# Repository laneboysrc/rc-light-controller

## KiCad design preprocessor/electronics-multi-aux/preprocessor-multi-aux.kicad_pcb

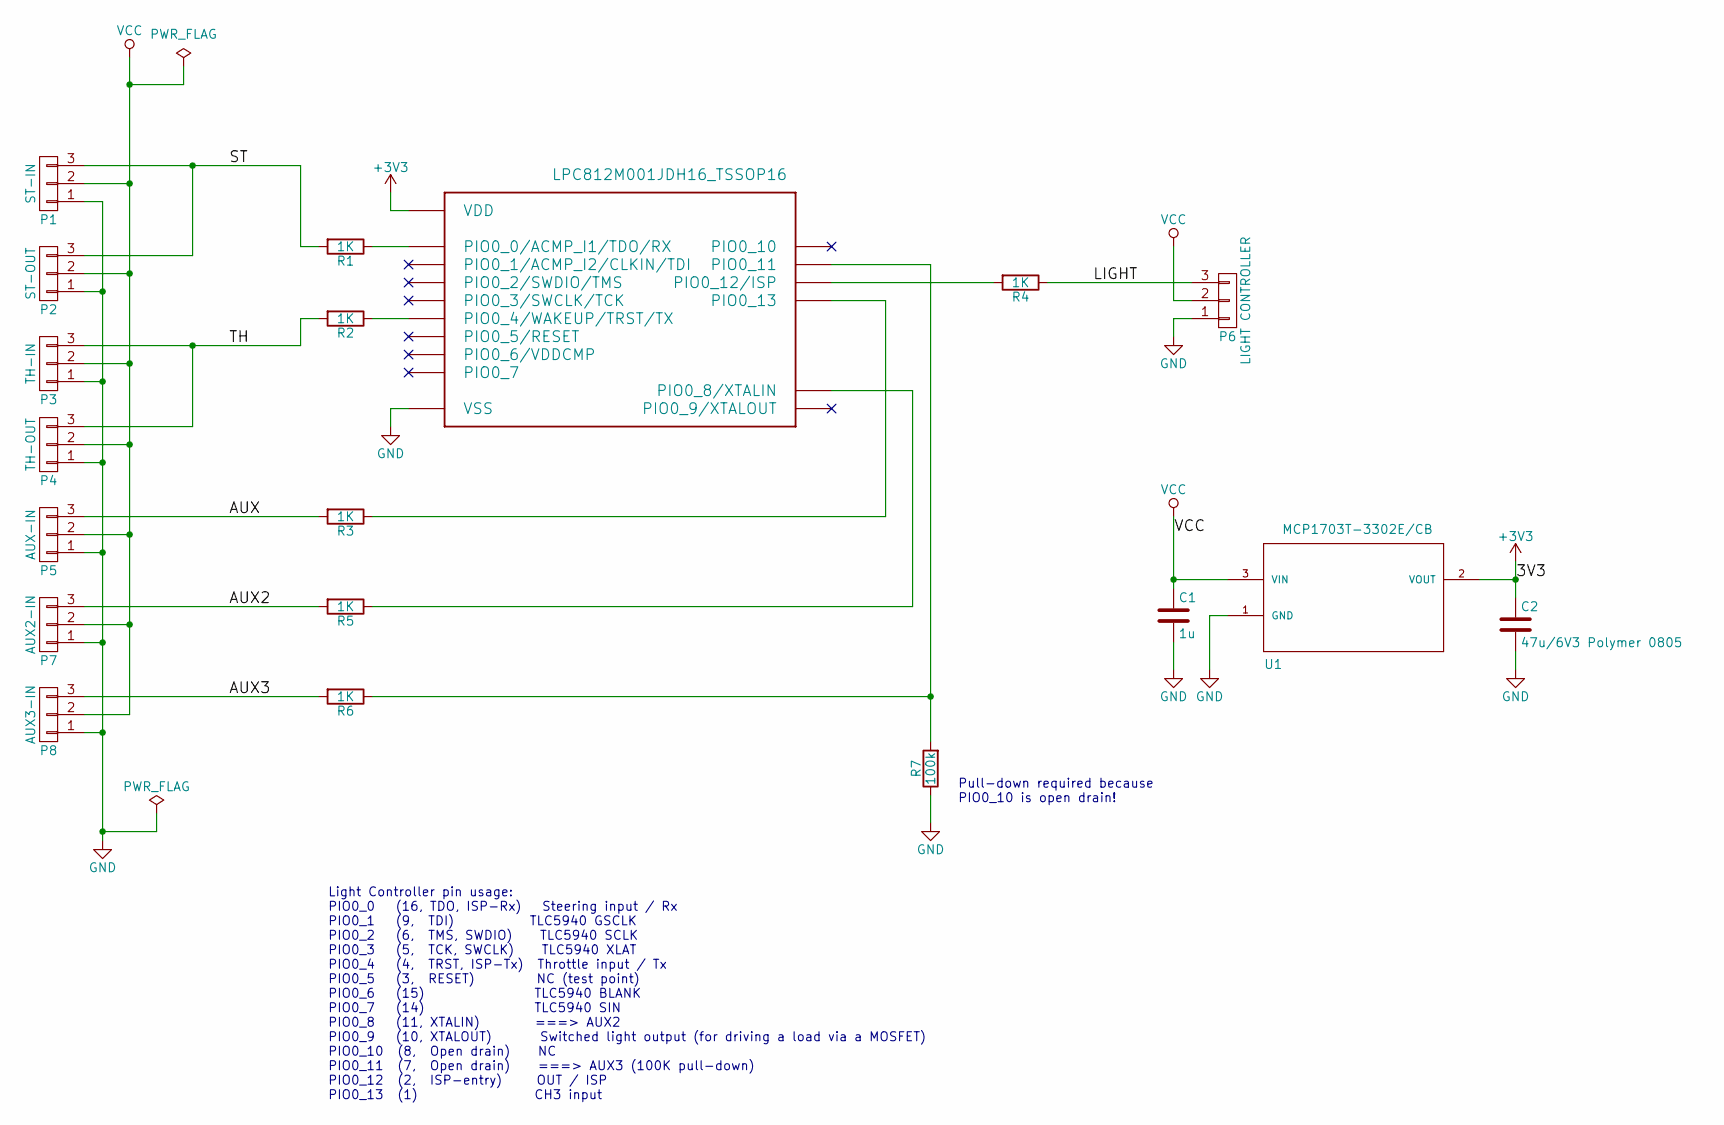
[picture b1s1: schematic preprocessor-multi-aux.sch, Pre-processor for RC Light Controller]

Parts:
C1: 1u; C_0805_2012Metric_Pad1.15x1.40mm_HandSolder
C2: 47u/6V3 Polymer 0805; C_0805_2012Metric_Pad1.15x1.40mm_HandSolder
P1: ST-IN; PinHeader_1x03_P2.54mm_Vertical
P2: ST-OUT; PinHeader_1x03_P2.54mm_Vertical
P3: TH-IN; PinHeader_1x03_P2.54mm_Vertical
P4: TH-OUT; PinHeader_1x03_P2.54mm_Vertical
P5: AUX-IN; PinHeader_1x03_P2.54mm_Vertical
P6: LIGHT CONTROLLER; PinHeader_1x03_P2.54mm_Vertical
P7: AUX2-IN; PinHeader_1x03_P2.54mm_Vertical
P8: AUX3-IN; PinHeader_1x03_P2.54mm_Vertical
R1, R2, R3, R4, R5, R6: 1K; R_0603_1608Metric_Pad1.05x0.95mm_HandSolder
R7: 100k; R_0603_1608Metric_Pad1.05x0.95mm_HandSolder
U1: MCP1703T-3302E/CB; SOT-23W_Handsoldering
U2: LPC812M001JDH16_TSSOP16; TSSOP-16_4.4x5mm_P0.65mm

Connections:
+3V3: C2.1, U1.2 (VOUT), U2.12 (VDD)
/AUX: P5.3, R3.2
/AUX2: P7.3, R5.2
/AUX3: P8.3, R6.2
/LIGHT: P6.3, R4.1
/ST: P1.3, P2.3, R1.2
/TH: P3.3, P4.3, R2.2
GND: C1.2, C2.2, P1.1, P2.1, P3.1, P4.1, P5.1, P6.1, P7.1, P8.1, R7.1, U1.1 (GND), U2.13 (VSS)
unnamed: R1.1, U2.16 (PIO0_0/ACMP_I1/TDO/RX)
unnamed: R2.1, U2.4 (PIO0_4/WAKEUP/TRST/TX)
unnamed: R3.1, U2.1 (PIO0_13)
unnamed: R4.2, U2.2 (PIO0_12/ISP)
unnamed: R5.1, U2.11 (PIO0_8/XTALIN)
unnamed: R6.1, R7.2, U2.7 (PIO0_11)
VCC: C1.1, P1.2, P2.2, P3.2, P4.2, P5.2, P6.2, P7.2, P8.2, U1.3 (VIN)

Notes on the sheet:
Light Controller pin usage: PIO0_0 (16, TDO, ISP-Rx) Steering input / Rx PIO0_1 (9, TDI) TLC5940 GSCLK PIO0_2 (6, TMS, SWDIO) TLC5940 SCLK PIO0_3 (5, TCK, SWCLK) TLC5940 XLAT PIO0_4 (4, TRST, ISP-Tx) Throttle input / Tx PIO0_5 (3, RESET) NC (test point) PIO0_6 (15) TLC5940 BLANK PIO0_7 (14) TLC5940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
Pull-down required because PIO0_10 is open drain!

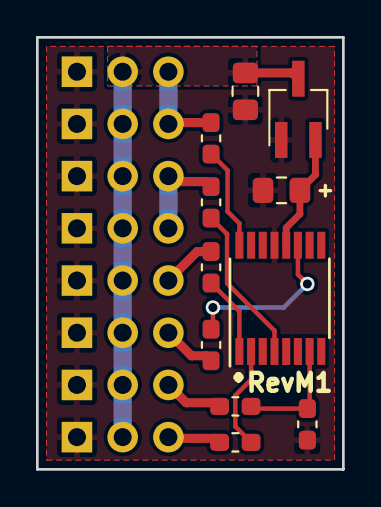
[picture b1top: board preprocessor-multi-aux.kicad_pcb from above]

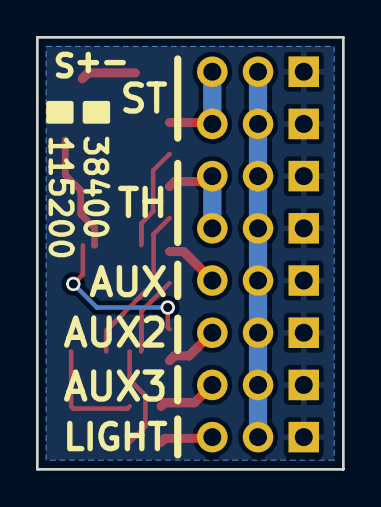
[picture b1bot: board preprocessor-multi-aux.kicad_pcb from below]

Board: 2 copper layers, 17.0 x 24.0 mm, 19 parts (8 on the bottom side), 15 nets.

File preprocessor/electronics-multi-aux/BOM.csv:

"Source:","/home/laneboysrc/projects/rc-light-controller/preprocessor/electronics-multi-aux/preprocessor-multi-aux.sch"
"Date:","Fri 10 Apr 2020 06:58:27 AM"
"Tool:","Eeschema 5.1.5-52549c5~86~ubuntu18.04.1"
"Generator:","/usr/share/kicad/plugins/bom_csv_grouped_by_value.py"
"Component Count:","19"

"Individual Components:"

"Item","Qty","Reference(s)","Value","LibPart","Footprint","Datasheet"
"","","C1","1u","preprocessor-multi-aux-rescue:C-preprocessor-rescue","Capacitor_SMD:C_0805_2012Metric_Pad1.15x1.40mm_HandSolder",""
"","","C2","47u/6V3 Polymer 0805","preprocessor-multi-aux-rescue:C-preprocessor-rescue","Capacitor_SMD:C_0805_2012Metric_Pad1.15x1.40mm_HandSolder",""
"","","P1","ST-IN","preprocessor-multi-aux-rescue:CONN_01X03-preprocessor-rescue","Connector_PinHeader_2.54mm:PinHeader_1x03_P2.54mm_Vertical",""
"","","P2","ST-OUT","preprocessor-multi-aux-rescue:CONN_01X03-preprocessor-rescue","Connector_PinHeader_2.54mm:PinHeader_1x03_P2.54mm_Vertical",""
"","","P3","TH-IN","preprocessor-multi-aux-rescue:CONN_01X03-preprocessor-rescue","Connector_PinHeader_2.54mm:PinHeader_1x03_P2.54mm_Vertical",""
"","","P4","TH-OUT","preprocessor-multi-aux-rescue:CONN_01X03-preprocessor-rescue","Connector_PinHeader_2.54mm:PinHeader_1x03_P2.54mm_Vertical",""
"","","P5","AUX-IN","preprocessor-multi-aux-rescue:CONN_01X03-preprocessor-rescue","Connector_PinHeader_2.54mm:PinHeader_1x03_P2.54mm_Vertical",""
"","","P6","LIGHT CONTROLLER","preprocessor-multi-aux-rescue:CONN_01X03-preprocessor-rescue","Connector_PinHeader_2.54mm:PinHeader_1x03_P2.54mm_Vertical",""
"","","P7","AUX2-IN","preprocessor-multi-aux-rescue:CONN_01X03-preprocessor-rescue","Connector_PinHeader_2.54mm:PinHeader_1x03_P2.54mm_Vertical",""
"","","P8","AUX3-IN","preprocessor-multi-aux-rescue:CONN_01X03-preprocessor-rescue","Connector_PinHeader_2.54mm:PinHeader_1x03_P2.54mm_Vertical",""
"","","R1","1K","preprocessor-multi-aux-rescue:R-preprocessor-rescue","Resistor_SMD:R_0603_1608Metric_Pad1.05x0.95mm_HandSolder",""
"","","R2","1K","preprocessor-multi-aux-rescue:R-preprocessor-rescue","Resistor_SMD:R_0603_1608Metric_Pad1.05x0.95mm_HandSolder",""
"","","R3","1K","preprocessor-multi-aux-rescue:R-preprocessor-rescue","Resistor_SMD:R_0603_1608Metric_Pad1.05x0.95mm_HandSolder",""
"","","R4","1K","preprocessor-multi-aux-rescue:R-preprocessor-rescue","Resistor_SMD:R_0603_1608Metric_Pad1.05x0.95mm_HandSolder",""
"","","R5","1K","preprocessor-multi-aux-rescue:R-preprocessor-rescue","Resistor_SMD:R_0603_1608Metric_Pad1.05x0.95mm_HandSolder",""
"","","R6","1K","preprocessor-multi-aux-rescue:R-preprocessor-rescue","Resistor_SMD:R_0603_1608Metric_Pad1.05x0.95mm_HandSolder",""
"","","R7","100k","preprocessor-multi-aux-rescue:R-preprocessor-rescue","Resistor_SMD:R_0603_1608Metric_Pad1.05x0.95mm_HandSolder",""
"","","U1","MCP1703T-3302E/CB","preprocessor-multi-aux-rescue:MCP1703T-3302E_CB-preprocessor-rescue","Package_TO_SOT_SMD:SOT-23W_Handsoldering",""
"","","U2","LPC812M001JDH16_TSSOP16","WLA-NXP-LPC:LPC811M001JDH16_TSSOP16","Package_SO:TSSOP-16_4.4x5mm_P0.65mm",""



"Collated Components:"

"Item","Qty","Reference(s)","Value","LibPart","Footprint","Datasheet"
"1","1","C1","1u","preprocessor-multi-aux-rescue:C-preprocessor-rescue","Capacitor_SMD:C_0805_2012Metric_Pad1.15x1.40mm_HandSolder",""
"2","1","C2","47u/6V3 Polymer 0805","preprocessor-multi-aux-rescue:C-preprocessor-rescue","Capacitor_SMD:C_0805_2012Metric_Pad1.15x1.40mm_HandSolder",""
"3","1","P1","ST-IN","preprocessor-multi-aux-rescue:CONN_01X03-preprocessor-rescue","Connector_PinHeader_2.54mm:PinHeader_1x03_P2.54mm_Vertical",""
"4","1","P2","ST-OUT","preprocessor-multi-aux-rescue:CONN_01X03-preprocessor-rescue","Connector_PinHeader_2.54mm:PinHeader_1x03_P2.54mm_Vertical",""
"5","1","P3","TH-IN","preprocessor-multi-aux-rescue:CONN_01X03-preprocessor-rescue","Connector_PinHeader_2.54mm:PinHeader_1x03_P2.54mm_Vertical",""
"6","1","P4","TH-OUT","preprocessor-multi-aux-rescue:CONN_01X03-preprocessor-rescue","Connector_PinHeader_2.54mm:PinHeader_1x03_P2.54mm_Vertical",""
"7","1","P5","AUX-IN","preprocessor-multi-aux-rescue:CONN_01X03-preprocessor-rescue","Connector_PinHeader_2.54mm:PinHeader_1x03_P2.54mm_Vertical",""
"8","1","P6","LIGHT CONTROLLER","preprocessor-multi-aux-rescue:CONN_01X03-preprocessor-rescue","Connector_PinHeader_2.54mm:PinHeader_1x03_P2.54mm_Vertical",""
"9","1","P7","AUX2-IN","preprocessor-multi-aux-rescue:CONN_01X03-preprocessor-rescue","Connector_PinHeader_2.54mm:PinHeader_1x03_P2.54mm_Vertical",""
"10","1","P8","AUX3-IN","preprocessor-multi-aux-rescue:CONN_01X03-preprocessor-rescue","Connector_PinHeader_2.54mm:PinHeader_1x03_P2.54mm_Vertical",""
"11","6","R1, R2, R3, R4, R5, R6","1K","preprocessor-multi-aux-rescue:R-preprocessor-rescue","Resistor_SMD:R_0603_1608Metric_Pad1.05x0.95mm_HandSolder",""
"12","1","R7","100k","preprocessor-multi-aux-rescue:R-preprocessor-rescue","Resistor_SMD:R_0603_1608Metric_Pad1.05x0.95mm_HandSolder",""
"13","1","U1","MCP1703T-3302E/CB","preprocessor-multi-aux-rescue:MCP1703T-3302E_CB-preprocessor-rescue","Package_TO_SOT_SMD:SOT-23W_Handsoldering",""
"14","1","U2","LPC812M001JDH16_TSSOP16","WLA-NXP-LPC:LPC811M001JDH16_TSSOP16","Package_SO:TSSOP-16_4.4x5mm_P0.65mm",""

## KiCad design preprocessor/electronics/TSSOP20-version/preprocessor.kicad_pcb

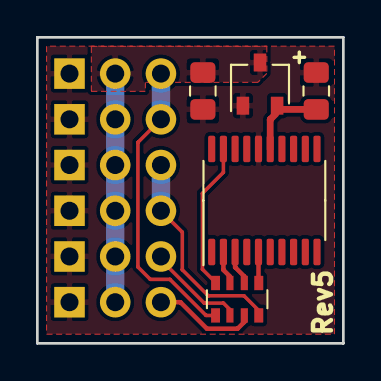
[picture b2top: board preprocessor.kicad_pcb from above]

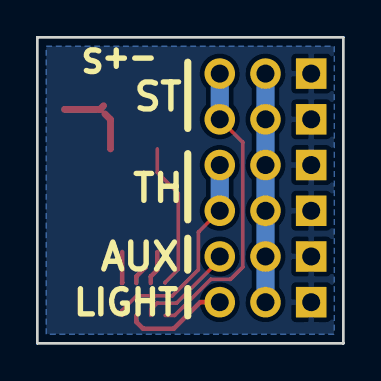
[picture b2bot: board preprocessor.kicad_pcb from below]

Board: 2 copper layers, 17.0 x 17.0 mm, 11 parts (6 on the bottom side), 11 nets.

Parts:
C1: 1u; C_0805_2012Metric_Pad1.15x1.40mm_HandSolder
C2: 47u/6V3 Polymer 0805; C_0805_2012Metric_Pad1.15x1.40mm_HandSolder
P1: ST-IN; Pin_Header_Straight_1x03_Pitch2.54mm
P2: ST-OUT; Pin_Header_Straight_1x03_Pitch2.54mm
P3: TH-IN; Pin_Header_Straight_1x03_Pitch2.54mm
P4: TH-OUT; Pin_Header_Straight_1x03_Pitch2.54mm
P5: AUX-IN; Pin_Header_Straight_1x03_Pitch2.54mm
P6: LIGHT CONTROLLER; Pin_Header_Straight_1x03_Pitch2.54mm
RN1: 1K; R_Array_Convex_4x0603
U1: MCP1703T-3302E/CB; SOT-23W
U2: LPC812M001JDH20_TSSOP20; TSSOP-20_4.4x6.5mm_P0.65mm

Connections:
+3V3: C2.1, U1.2, U2.15
/AUX: RN1.7, U2.2
/AUX_IN: P5.3, RN1.2
/LIGHT: RN1.6, U2.3
/LIGHT_OUT: P6.3, RN1.3
/ST: RN1.8, U2.19
/ST_IN: P1.3, P2.3, RN1.1
/TH: RN1.5, U2.5
/TH_IN: P3.3, P4.3, RN1.4
GND: C1.2, C2.2, P1.1, P2.1, P3.1, P4.1, P5.1, P6.1, U1.1, U2.16
VCC: C1.1, P1.2, P2.2, P3.2, P4.2, P5.2, P6.2, U1.3

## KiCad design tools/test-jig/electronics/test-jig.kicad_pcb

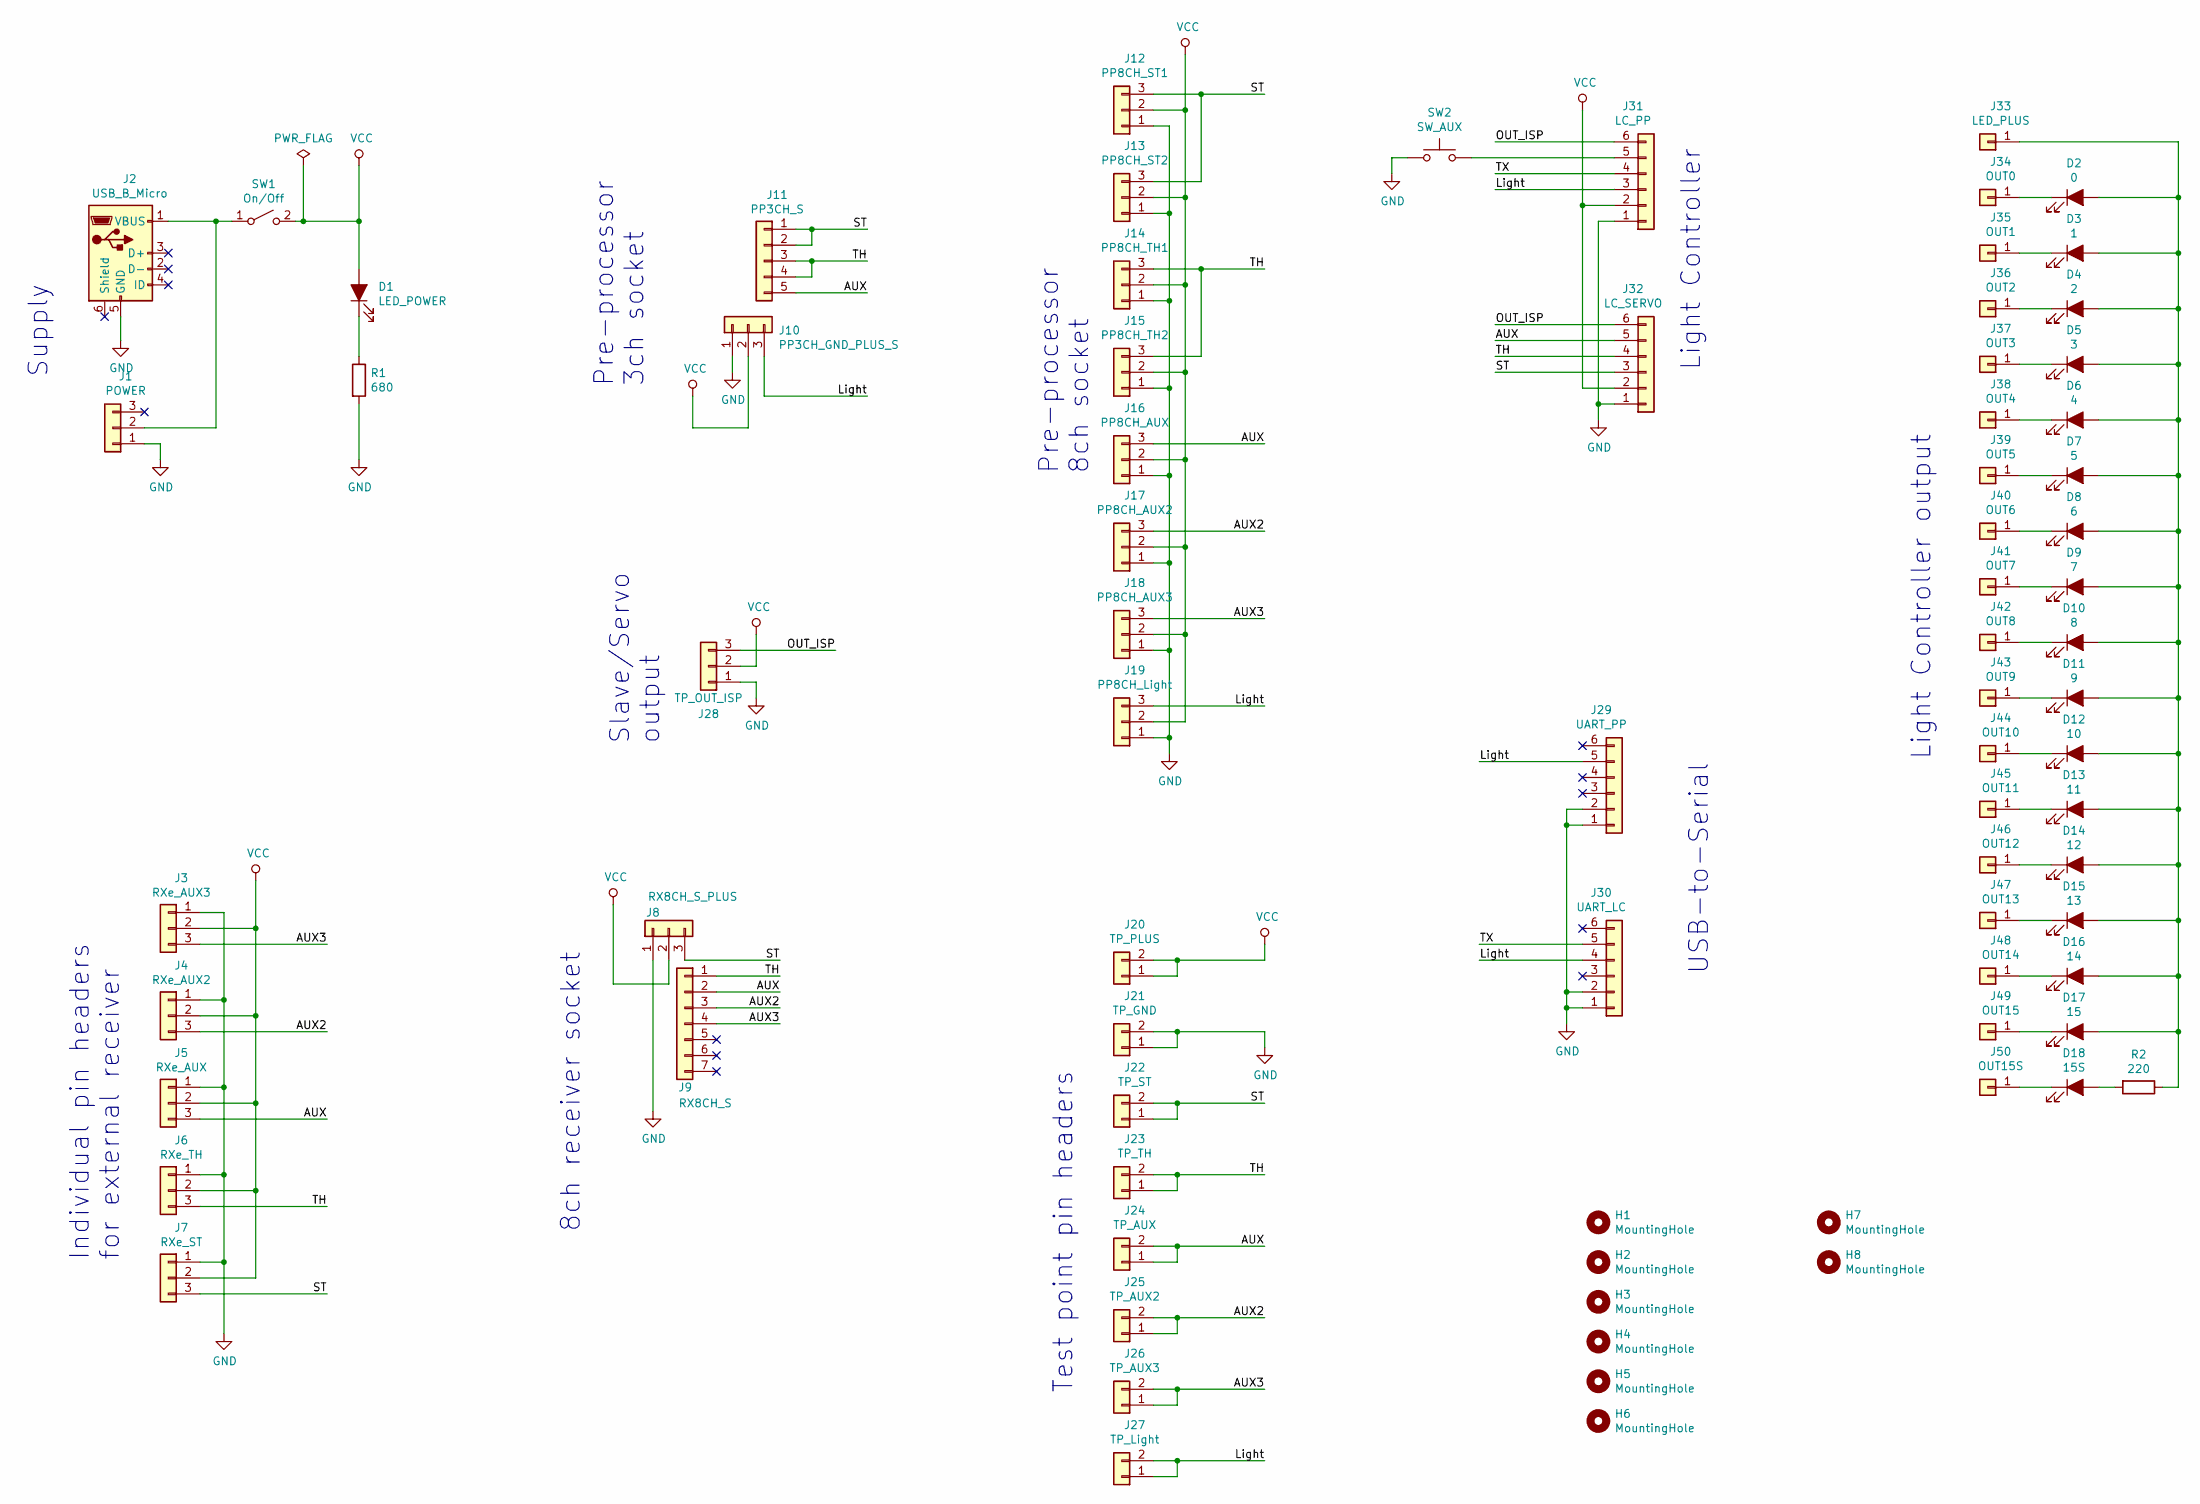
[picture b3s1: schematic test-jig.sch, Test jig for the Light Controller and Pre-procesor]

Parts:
D1: LED_POWER; LED_1206_3216Metric_Pad1.42x1.75mm_HandSolder
D2: 0; LED_1206_3216Metric_Pad1.42x1.75mm_HandSolder
D3: 1; LED_1206_3216Metric_Pad1.42x1.75mm_HandSolder
D4: 2; LED_1206_3216Metric_Pad1.42x1.75mm_HandSolder
D5: 3; LED_1206_3216Metric_Pad1.42x1.75mm_HandSolder
D6: 4; LED_1206_3216Metric_Pad1.42x1.75mm_HandSolder
D7: 5; LED_1206_3216Metric_Pad1.42x1.75mm_HandSolder
D8: 6; LED_1206_3216Metric_Pad1.42x1.75mm_HandSolder
D9: 7; LED_1206_3216Metric_Pad1.42x1.75mm_HandSolder
D10: 8; LED_1206_3216Metric_Pad1.42x1.75mm_HandSolder
D11: 9; LED_1206_3216Metric_Pad1.42x1.75mm_HandSolder
D12: 10; LED_1206_3216Metric_Pad1.42x1.75mm_HandSolder
D13: 11; LED_1206_3216Metric_Pad1.42x1.75mm_HandSolder
D14: 12; LED_1206_3216Metric_Pad1.42x1.75mm_HandSolder
D15: 13; LED_1206_3216Metric_Pad1.42x1.75mm_HandSolder
D16: 14; LED_1206_3216Metric_Pad1.42x1.75mm_HandSolder
D17: 15; LED_1206_3216Metric_Pad1.42x1.75mm_HandSolder
D18: 15S; LED_1206_3216Metric_Pad1.42x1.75mm_HandSolder
H1, H2, H3, H4, H5, H6: MountingHole; MountingHole_3.2mm_M3_ISO7380
H7, H8: MountingHole; MountingHole_2.2mm_M2_ISO7380
J1: POWER; PinHeader_1x03_P2.54mm_Vertical
J2: USB_B_Micro; PinHeader_1x05_P2.54mm_Horizontal
J3: RXe_AUX3; PinHeader_1x03_P2.54mm_Vertical
J4: RXe_AUX2; PinHeader_1x03_P2.54mm_Vertical
J5: RXe_AUX; PinHeader_1x03_P2.54mm_Vertical
J6: RXe_TH; PinHeader_1x03_P2.54mm_Vertical
J7: RXe_ST; PinHeader_1x03_P2.54mm_Vertical
J8: RX8CH_S_PLUS; PinSocket_1x03_P2.54mm_Vertical
J9: RX8CH_S; PinSocket_1x07_P2.54mm_Vertical
J10: PP3CH_GND_PLUS_S; PinSocket_1x03_P2.54mm_Vertical
J11: PP3CH_S; PinSocket_1x05_P2.54mm_Vertical
J12: PP8CH_ST1; PinSocket_1x03_P2.54mm_Vertical
J13: PP8CH_ST2; PinSocket_1x03_P2.54mm_Vertical
J14: PP8CH_TH1; PinSocket_1x03_P2.54mm_Vertical
J15: PP8CH_TH2; PinSocket_1x03_P2.54mm_Vertical
J16: PP8CH_AUX; PinSocket_1x03_P2.54mm_Vertical
J17: PP8CH_AUX2; PinSocket_1x03_P2.54mm_Vertical
J18: PP8CH_AUX3; PinSocket_1x03_P2.54mm_Vertical
J19: PP8CH_Light; PinSocket_1x03_P2.54mm_Vertical
J20: TP_PLUS; PinHeader_1x02_P2.54mm_Vertical
J21: TP_GND; PinHeader_1x02_P2.54mm_Vertical
J22: TP_ST; PinHeader_1x02_P2.54mm_Vertical
J23: TP_TH; PinHeader_1x02_P2.54mm_Vertical
J24: TP_AUX; PinHeader_1x02_P2.54mm_Vertical
J25: TP_AUX2; PinHeader_1x02_P2.54mm_Vertical
J26: TP_AUX3; PinHeader_1x02_P2.54mm_Vertical
J27: TP_Light; PinHeader_1x02_P2.54mm_Vertical
J28: TP_OUT_ISP; PinHeader_1x03_P2.54mm_Vertical
J29: UART_PP; PinSocket_1x06_P2.54mm_Horizontal
J30: UART_LC; PinSocket_1x06_P2.54mm_Horizontal
J31: LC_PP; PinHeader_1x06_P2.54mm_Vertical
J32: LC_SERVO; PinHeader_1x06_P2.54mm_Vertical
J33: LED_PLUS; Pogo_pin_Drill1mm
J34: OUT0; Pogo_pin_Drill1mm
J35: OUT1; Pogo_pin_Drill1mm
J36: OUT2; Pogo_pin_Drill1mm
J37: OUT3; Pogo_pin_Drill1mm
J38: OUT4; Pogo_pin_Drill1mm
J39: OUT5; Pogo_pin_Drill1mm
J40: OUT6; Pogo_pin_Drill1mm
J41: OUT7; Pogo_pin_Drill1mm
J42: OUT8; Pogo_pin_Drill1mm
J43: OUT9; Pogo_pin_Drill1mm
J44: OUT10; Pogo_pin_Drill1mm
J45: OUT11; Pogo_pin_Drill1mm
J46: OUT12; Pogo_pin_Drill1mm
J47: OUT13; Pogo_pin_Drill1mm
J48: OUT14; Pogo_pin_Drill1mm
J49: OUT15; Pogo_pin_Drill1mm
J50: OUT15S; Pogo_pin_Drill1mm
R1: 680; R_0805_2012Metric_Pad1.15x1.40mm_HandSolder
R2: 220; R_0805_2012Metric_Pad1.15x1.40mm_HandSolder
SW1: On/Off; PinSocket_2x03_P2.54mm_Vertical
SW2: SW_AUX; SW_PUSH_6mm_H5mm

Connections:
/AUX: J5.3, J9.2, J11.5, J16.3, J24.1, J24.2, J32.5
/AUX2: J4.3, J9.3, J17.3, J25.1, J25.2
/AUX3: J3.3, J9.4, J18.3, J26.1, J26.2
/Light: J10.3, J19.3, J27.1, J27.2, J29.5, J30.4, J31.3
/OUT_ISP: J28.3, J31.6, J32.6
/ST: J7.3, J8.3, J11.1, J11.2, J12.3, J13.3, J22.1, J22.2, J32.3
/TH: J6.3, J9.1, J11.3, J11.4, J14.3, J15.3, J23.1, J23.2, J32.4
/TX: J30.5, J31.4
GND: J1.1, J2.5 (GND), J3.1, J4.1, J5.1, J6.1, J7.1, J8.1, J10.1, J12.1, J13.1, J14.1, J15.1, J16.1, J17.1, J18.1, J19.1, J21.1, J21.2, J28.1, J29.1, J29.2, J30.1, J30.2, J31.1, J32.1, R1.2, SW2.1
unnamed: D1.1 (K), R1.1
unnamed: D2.1 (K), J34.1
unnamed: D3.1 (K), J35.1
unnamed: D4.1 (K), J36.1
unnamed: D5.1 (K), J37.1
unnamed: D6.1 (K), J38.1
unnamed: D7.1 (K), J39.1
unnamed: D8.1 (K), J40.1
unnamed: D9.1 (K), J41.1
unnamed: D10.1 (K), J42.1
unnamed: D2.2 (A), D3.2 (A), D4.2 (A), D5.2 (A), D6.2 (A), D7.2 (A), D8.2 (A), D9.2 (A), D10.2 (A), D11.2 (A), D12.2 (A), D13.2 (A), D14.2 (A), D15.2 (A), D16.2 (A), D17.2 (A), J33.1, R2.1
unnamed: D11.1 (K), J43.1
unnamed: D12.1 (K), J44.1
unnamed: D13.1 (K), J45.1
unnamed: D14.1 (K), J46.1
unnamed: D15.1 (K), J47.1
unnamed: D16.1 (K), J48.1
unnamed: D17.1 (K), J49.1
unnamed: D18.1 (K), J50.1
unnamed: D18.2 (A), R2.2
unnamed: J1.2, J2.1 (VBUS), SW1.1 (A)
unnamed: J31.5, SW2.2
VCC: D1.2 (A), J3.2, J4.2, J5.2, J6.2, J7.2, J8.2, J10.2, J12.2, J13.2, J14.2, J15.2, J16.2, J17.2, J18.2, J19.2, J20.1, J20.2, J28.2, J31.2, J32.2, SW1.2 (B)

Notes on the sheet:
Individual pin headers for external receiver
8ch receiver socket
Supply
Pre-processor 3ch socket
Pre-processor 8ch socket
Light Controller
USB-to-Serial
Test point pin headers
Light Controller output
Slave/Servo output

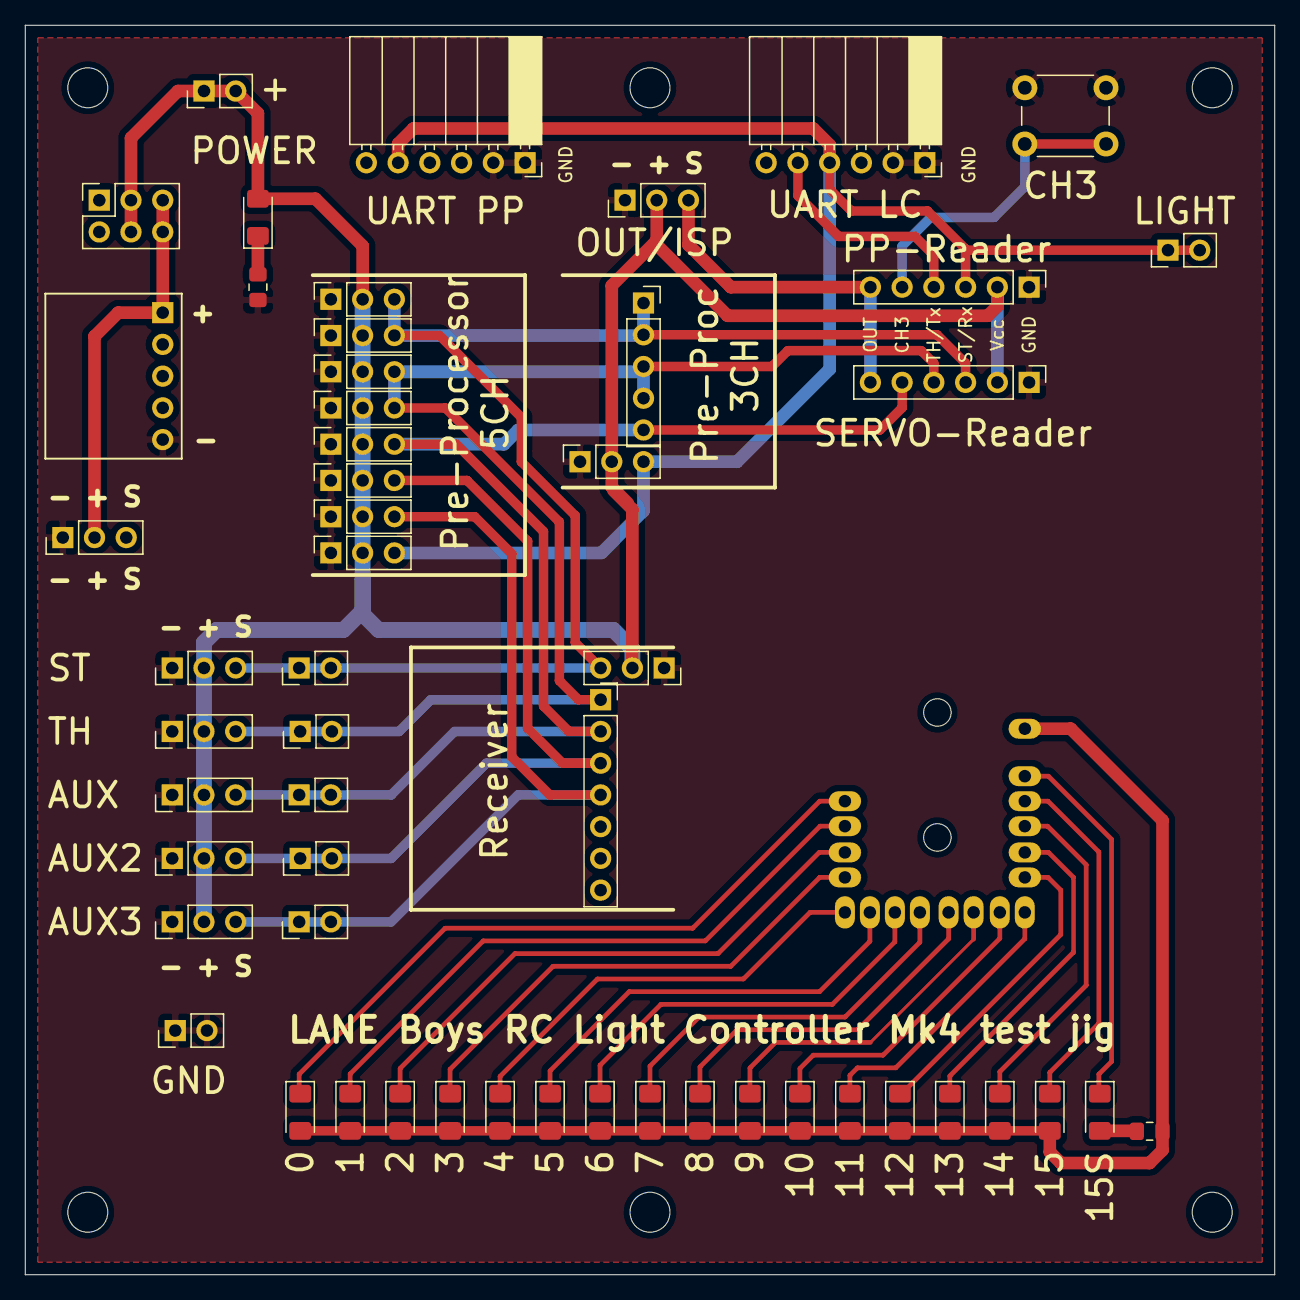
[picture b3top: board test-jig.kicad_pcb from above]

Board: 2 copper layers, 100.0 x 100.0 mm, 80 parts (1 on the bottom side), 32 nets.
